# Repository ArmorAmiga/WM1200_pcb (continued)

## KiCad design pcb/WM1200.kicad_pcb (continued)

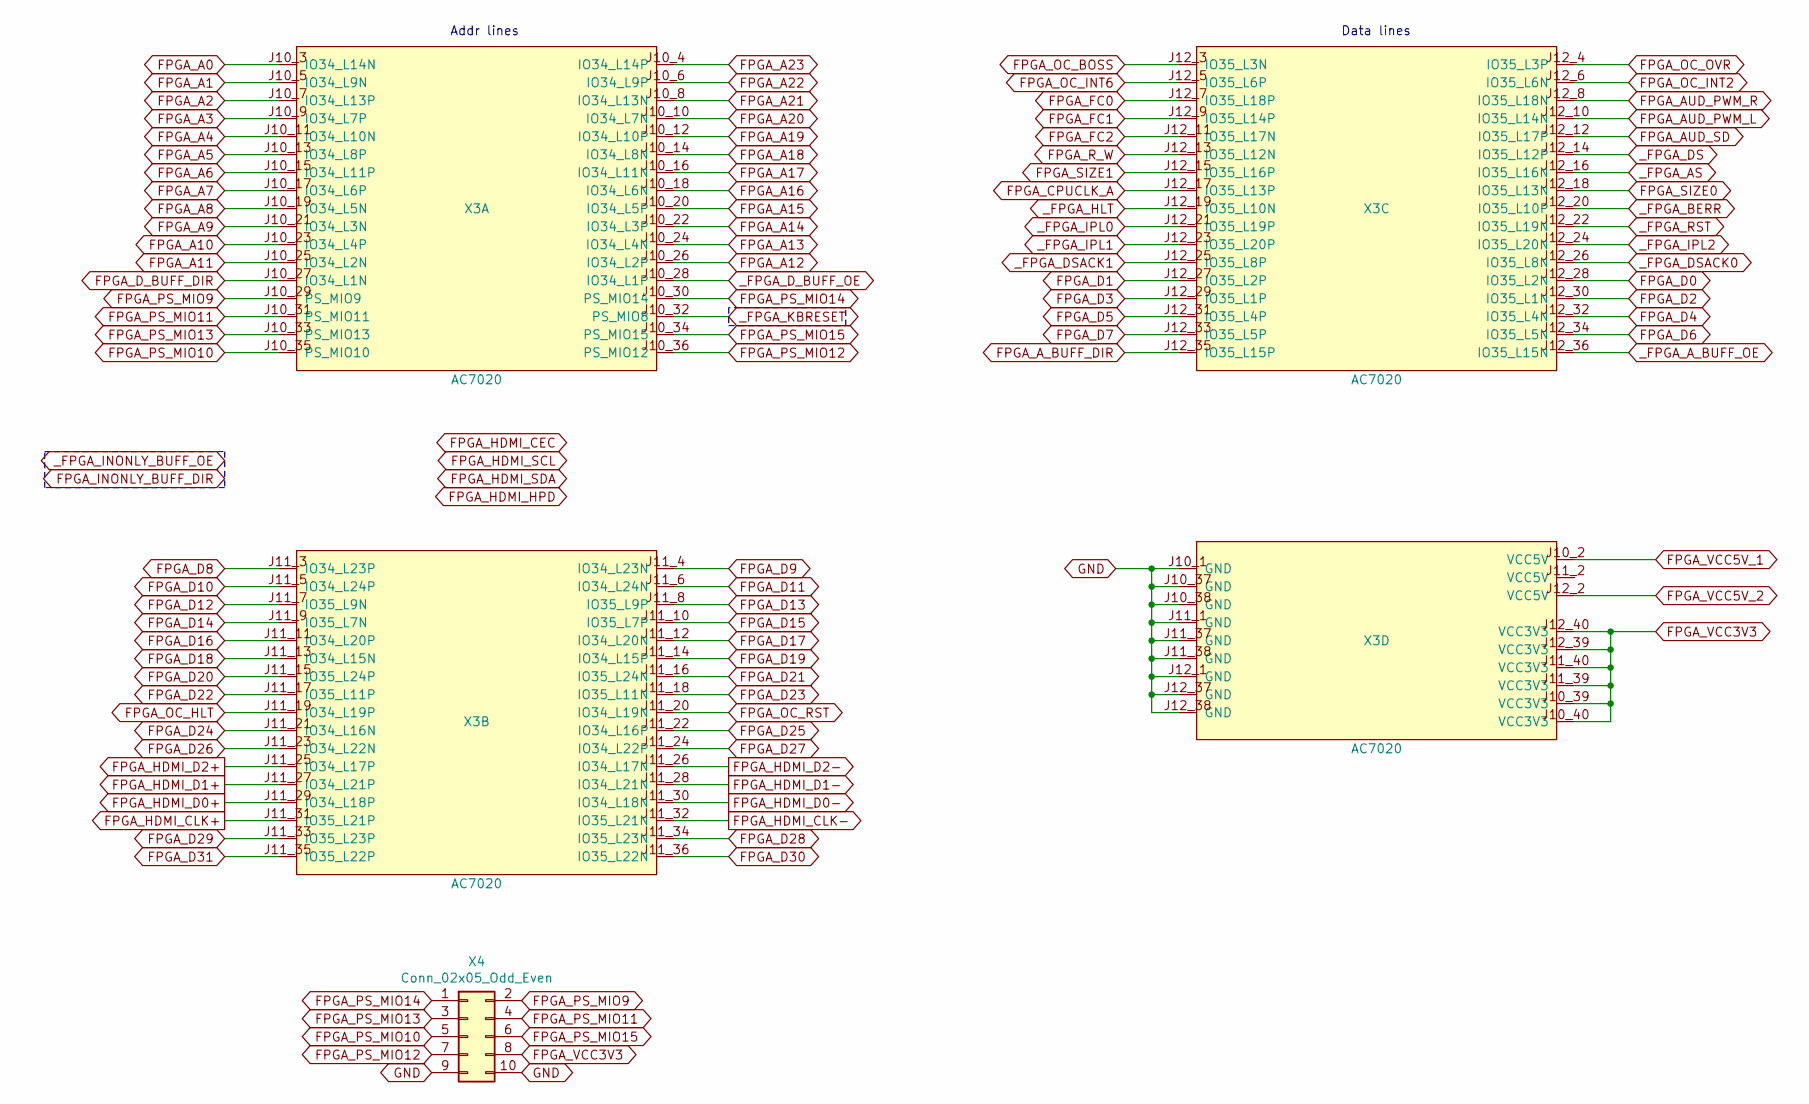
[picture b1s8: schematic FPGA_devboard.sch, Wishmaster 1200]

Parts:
X3: AC7020; ac7020
X4: Conn_02x05_Odd_Even; PinHeader_2x05_P2.54mm_Vertical

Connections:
FPGA_A0: X3.J10_3 (IO34_L14N); also elsewhere on the board
FPGA_A1: X3.J10_5 (IO34_L9N); also elsewhere on the board
FPGA_A2: X3.J10_7 (IO34_L13P); also elsewhere on the board
FPGA_A3: X3.J10_9 (IO34_L7P); also elsewhere on the board
FPGA_A4: X3.J10_11 (IO34_L10N); also elsewhere on the board
FPGA_A5: X3.J10_13 (IO34_L8P); also elsewhere on the board
FPGA_A6: X3.J10_15 (IO34_L11P); also elsewhere on the board
FPGA_A7: X3.J10_17 (IO34_L6P); also elsewhere on the board
FPGA_A8: X3.J10_19 (IO34_L5N); also elsewhere on the board
FPGA_A9: X3.J10_21 (IO34_L3N); also elsewhere on the board
FPGA_A10: X3.J10_23 (IO34_L4P); also elsewhere on the board
FPGA_A11: X3.J10_25 (IO34_L2N); also elsewhere on the board
FPGA_A12: X3.J10_26 (IO34_L2P); also elsewhere on the board
FPGA_A13: X3.J10_24 (IO34_L4N); also elsewhere on the board
FPGA_A14: X3.J10_22 (IO34_L3P); also elsewhere on the board
FPGA_A15: X3.J10_20 (IO34_L5P); also elsewhere on the board
FPGA_A16: X3.J10_18 (IO34_L6N); also elsewhere on the board
FPGA_A17: X3.J10_16 (IO34_L11N); also elsewhere on the board
FPGA_A18: X3.J10_14 (IO34_L8N); also elsewhere on the board
FPGA_A19: X3.J10_12 (IO34_L10P); also elsewhere on the board
FPGA_A20: X3.J10_10 (IO34_L7N); also elsewhere on the board
FPGA_A21: X3.J10_8 (IO34_L13N); also elsewhere on the board
FPGA_A22: X3.J10_6 (IO34_L9P); also elsewhere on the board
FPGA_A23: X3.J10_4 (IO34_L14P); also elsewhere on the board
FPGA_AUD_PWM_L: X3.J12_10 (IO35_L14N); also elsewhere on the board
FPGA_AUD_PWM_R: X3.J12_8 (IO35_L18N); also elsewhere on the board
FPGA_AUD_SD: X3.J12_12 (IO35_L17P); also elsewhere on the board
FPGA_A_BUFF_DIR: X3.J12_35 (IO35_L15P); also elsewhere on the board
FPGA_CPUCLK_A: X3.J12_17 (IO35_L13P); also elsewhere on the board
FPGA_D0: X3.J12_28 (IO35_L2N); also elsewhere on the board
FPGA_D1: X3.J12_27 (IO35_L2P); also elsewhere on the board
FPGA_D2: X3.J12_30 (IO35_L1N); also elsewhere on the board
FPGA_D3: X3.J12_29 (IO35_L1P); also elsewhere on the board
FPGA_D4: X3.J12_32 (IO35_L4N); also elsewhere on the board
FPGA_D5: X3.J12_31 (IO35_L4P); also elsewhere on the board
FPGA_D6: X3.J12_34 (IO35_L5N); also elsewhere on the board
FPGA_D7: X3.J12_33 (IO35_L5P); also elsewhere on the board
FPGA_D8: X3.J11_3 (IO34_L23P); also elsewhere on the board
FPGA_D9: X3.J11_4 (IO34_L23N); also elsewhere on the board
FPGA_D10: X3.J11_5 (IO34_L24P); also elsewhere on the board
FPGA_D11: X3.J11_6 (IO34_L24N); also elsewhere on the board
FPGA_D12: X3.J11_7 (IO35_L9N); also elsewhere on the board
FPGA_D13: X3.J11_8 (IO35_L9P); also elsewhere on the board
FPGA_D14: X3.J11_9 (IO35_L7N); also elsewhere on the board
FPGA_D15: X3.J11_10 (IO35_L7P); also elsewhere on the board
FPGA_D16: X3.J11_11 (IO34_L20P); also elsewhere on the board
FPGA_D17: X3.J11_12 (IO34_L20N); also elsewhere on the board
FPGA_D18: X3.J11_13 (IO34_L15N); also elsewhere on the board
FPGA_D19: X3.J11_14 (IO34_L15P); also elsewhere on the board
FPGA_D20: X3.J11_15 (IO35_L24P); also elsewhere on the board
FPGA_D21: X3.J11_16 (IO35_L24N); also elsewhere on the board
FPGA_D22: X3.J11_17 (IO35_L11P); also elsewhere on the board
FPGA_D23: X3.J11_18 (IO35_L11N); also elsewhere on the board
FPGA_D24: X3.J11_21 (IO34_L16N); also elsewhere on the board
FPGA_D25: X3.J11_22 (IO34_L16P); also elsewhere on the board
FPGA_D26: X3.J11_23 (IO34_L22N); also elsewhere on the board
FPGA_D27: X3.J11_24 (IO34_L22P); also elsewhere on the board
FPGA_D28: X3.J11_34 (IO35_L23N); also elsewhere on the board
FPGA_D29: X3.J11_33 (IO35_L23P); also elsewhere on the board
FPGA_D30: X3.J11_36 (IO35_L22N); also elsewhere on the board
FPGA_D31: X3.J11_35 (IO35_L22P); also elsewhere on the board
FPGA_D_BUFF_DIR: X3.J10_27 (IO34_L1N); also elsewhere on the board
FPGA_FC0: X3.J12_7 (IO35_L18P); also elsewhere on the board
FPGA_FC1: X3.J12_9 (IO35_L14P); also elsewhere on the board
FPGA_FC2: X3.J12_11 (IO35_L17N); also elsewhere on the board
FPGA_HDMI_CLK+: X3.J11_31 (IO35_L21P); also elsewhere on the board
FPGA_HDMI_CLK-: X3.J11_32 (IO35_L21N); also elsewhere on the board
FPGA_HDMI_D0+: X3.J11_29 (IO34_L18P); also elsewhere on the board
FPGA_HDMI_D0-: X3.J11_30 (IO34_L18N); also elsewhere on the board
FPGA_HDMI_D1+: X3.J11_27 (IO34_L21P); also elsewhere on the board
FPGA_HDMI_D1-: X3.J11_28 (IO34_L21N); also elsewhere on the board
FPGA_HDMI_D2+: X3.J11_25 (IO34_L17P); also elsewhere on the board
FPGA_HDMI_D2-: X3.J11_26 (IO34_L17N); also elsewhere on the board
FPGA_OC_BOSS: X3.J12_3 (IO35_L3N); also elsewhere on the board
FPGA_OC_HLT: X3.J11_19 (IO34_L19P); also elsewhere on the board
FPGA_OC_INT2: X3.J12_6 (IO35_L6N); also elsewhere on the board
FPGA_OC_INT6: X3.J12_5 (IO35_L6P); also elsewhere on the board
FPGA_OC_OVR: X3.J12_4 (IO35_L3P); also elsewhere on the board
FPGA_OC_RST: X3.J11_20 (IO34_L19N); also elsewhere on the board
FPGA_PS_MIO9: X3.J10_29 (PS_MIO9), X4.2
FPGA_PS_MIO10: X3.J10_35 (PS_MIO10), X4.5
FPGA_PS_MIO11: X3.J10_31 (PS_MIO11), X4.4
FPGA_PS_MIO12: X3.J10_36 (PS_MIO12), X4.7
FPGA_PS_MIO13: X3.J10_33 (PS_MIO13), X4.3
FPGA_PS_MIO14: X3.J10_30 (PS_MIO14), X4.1
FPGA_PS_MIO15: X3.J10_34 (PS_MIO15), X4.6
FPGA_R_W: X3.J12_13 (IO35_L12N); also elsewhere on the board
FPGA_SIZE0: X3.J12_18 (IO35_L13N); also elsewhere on the board
FPGA_SIZE1: X3.J12_15 (IO35_L16P); also elsewhere on the board
FPGA_VCC3V3: X3.J10_39 (VCC3V3), X3.J10_40 (VCC3V3), X3.J11_39 (VCC3V3), X3.J11_40 (VCC3V3), X3.J12_39 (VCC3V3), X3.J12_40 (VCC3V3), X4.8; also elsewhere on the board
FPGA_VCC5V_1: X3.J10_2 (VCC5V); also elsewhere on the board
FPGA_VCC5V_2: X3.J12_2 (VCC5V); also elsewhere on the board
GND: X3.J10_1 (GND), X3.J10_37 (GND), X3.J10_38 (GND), X3.J11_1 (GND), X3.J11_37 (GND), X3.J11_38 (GND), X3.J12_1 (GND), X3.J12_37 (GND), X3.J12_38 (GND), X4.9, X4.10; also elsewhere on the board
_FPGA_AS: X3.J12_16 (IO35_L16N); also elsewhere on the board
_FPGA_A_BUFF_OE: X3.J12_36 (IO35_L15N); also elsewhere on the board
_FPGA_BERR: X3.J12_20 (IO35_L10P); also elsewhere on the board
_FPGA_DS: X3.J12_14 (IO35_L12P); also elsewhere on the board
_FPGA_DSACK0: X3.J12_26 (IO35_L8N); also elsewhere on the board
_FPGA_DSACK1: X3.J12_25 (IO35_L8P); also elsewhere on the board
_FPGA_D_BUFF_OE: X3.J10_28 (IO34_L1P); also elsewhere on the board
_FPGA_HLT: X3.J12_19 (IO35_L10N); also elsewhere on the board
_FPGA_IPL0: X3.J12_21 (IO35_L19P); also elsewhere on the board
_FPGA_IPL1: X3.J12_23 (IO35_L20P); also elsewhere on the board
_FPGA_IPL2: X3.J12_24 (IO35_L20N); also elsewhere on the board
_FPGA_KBRESET: X3.J10_32 (PS_MIO8); also elsewhere on the board
_FPGA_RST: X3.J12_22 (IO35_L19N); also elsewhere on the board

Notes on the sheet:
Data lines
Addr lines

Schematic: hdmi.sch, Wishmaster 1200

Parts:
C29, C30, C31: 0.1uF 35V; C_0603_1608Metric_Pad1.05x0.95mm_HandSolder
C32: 1nF 250V; C_0603_1608Metric_Pad1.05x0.95mm_HandSolder
R21, R22, R23, R25: 4.7k; R_0603_1608Metric_Pad1.05x0.95mm_HandSolder
R24: 1M; R_0603_1608Metric_Pad1.05x0.95mm_HandSolder
U7: TPD12S016PWR; TSSOP-24_4.4x7.8mm_P0.65mm
X5: HDMI_A; HDMI-19-02F

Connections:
FPGA_HDMI_CEC: U7.1 (CEC_A)
FPGA_HDMI_CLK+: U7.16 (CLK+), X5.10 (CK+); also elsewhere on the board
FPGA_HDMI_CLK-: U7.15 (CLK-), X5.12 (CK-); also elsewhere on the board
FPGA_HDMI_CT_HPD: R23.1, U7.12 (CT_HPD)
FPGA_HDMI_D0+: U7.18 (D0+), X5.7 (D0+); also elsewhere on the board
FPGA_HDMI_D0-: U7.17 (D0-), X5.9 (D0-); also elsewhere on the board
FPGA_HDMI_D1+: U7.21 (D1+), X5.4 (D1+); also elsewhere on the board
FPGA_HDMI_D1-: U7.20 (D1-), X5.6 (D1-); also elsewhere on the board
FPGA_HDMI_D2+: U7.23 (D2+), X5.1 (D2+); also elsewhere on the board
FPGA_HDMI_D2-: U7.22 (D2-), X5.3 (D2-); also elsewhere on the board
FPGA_HDMI_HPD: U7.4 (HPD_A)
FPGA_HDMI_LS_OE: R25.2, U7.5 (LS_OE)
FPGA_HDMI_SCL: R21.1, U7.2 (SCL_A)
FPGA_HDMI_SDA: R22.2, U7.3 (SDA_A)
FPGA_VCC3V3: C31.1, R21.2, R22.1, R23.2, R25.1, U7.24 (VCCA); also elsewhere on the board
FPGA_VCC5V_1: C30.1, U7.11 (VCC5V); also elsewhere on the board
GND: C29.2, C30.2, C31.2, C32.2, R24.2, U7.6 (GND), U7.14 (GND), U7.19 (GND), X5.2 (D2S), X5.5 (D1S), X5.8 (D0S), X5.11 (CKS), X5.17 (GND); also elsewhere on the board
unnamed: C29.1, U7.13 (5V_OUT), X5.18 (+5V)
unnamed: C32.1, R24.1, X5.SH
unnamed: U7.7 (CEC_B), X5.13 (CEC)
unnamed: U7.8 (SCL_B), X5.15 (SCL)
unnamed: U7.9 (SDA_B), X5.16 (SDA)
unnamed: U7.10 (HPD_B), X5.19 (HPD)

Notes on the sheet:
i2c pullup (not sure if i2c will be used here) tpd12s016 seems to have it's own pullups -- not needed?
enable pullups for tpd12s016

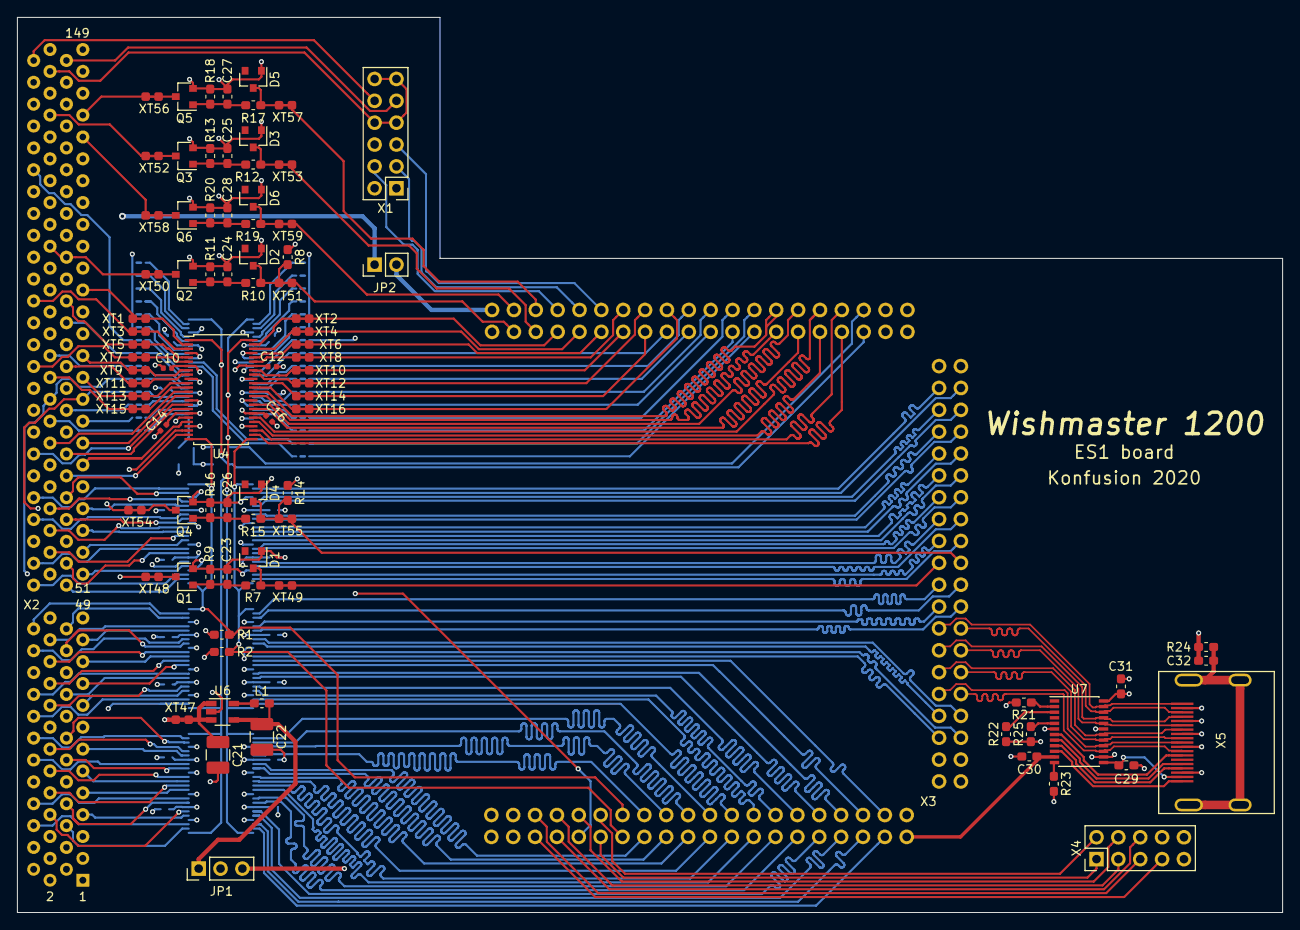
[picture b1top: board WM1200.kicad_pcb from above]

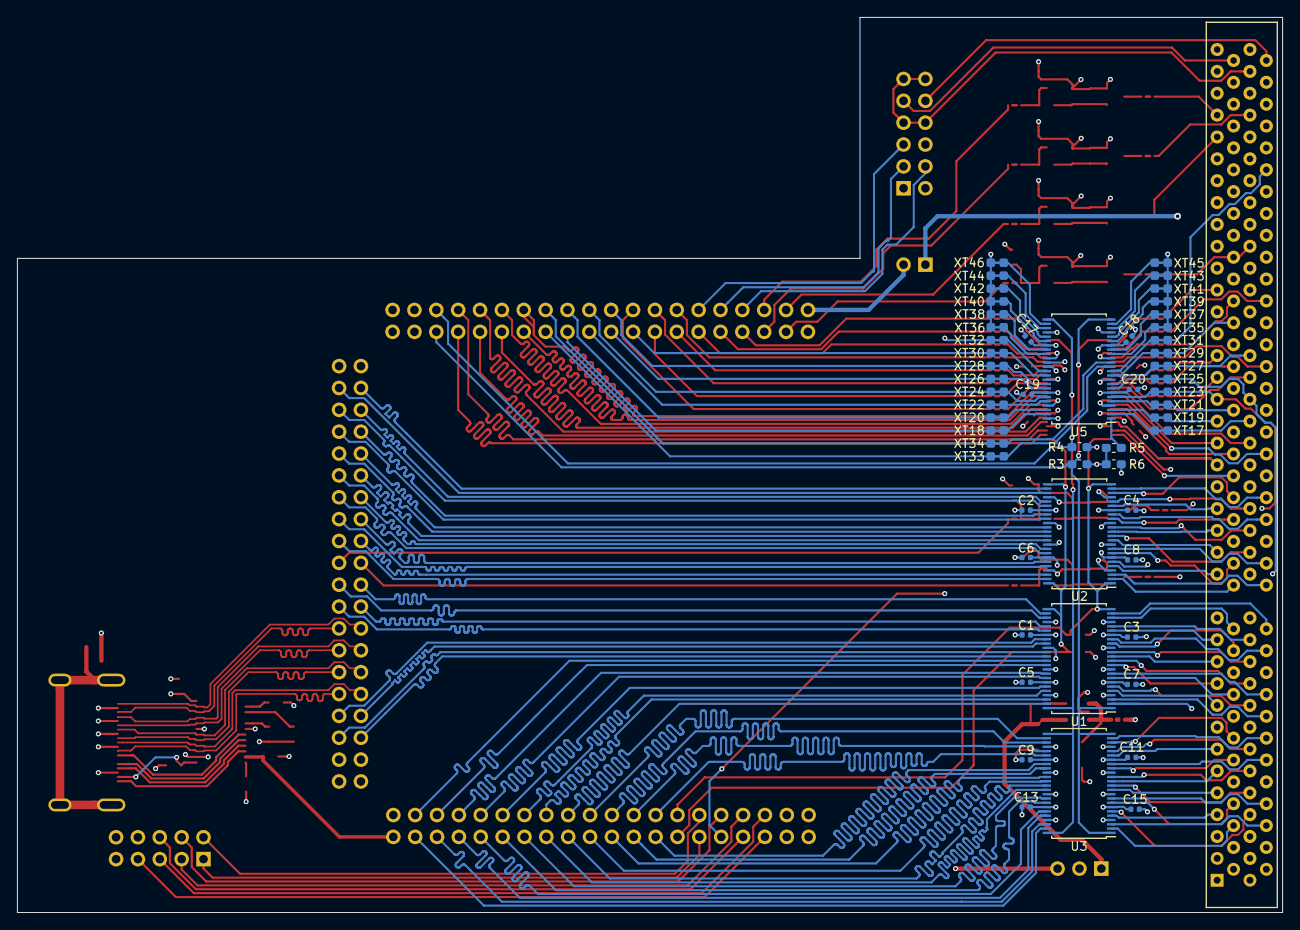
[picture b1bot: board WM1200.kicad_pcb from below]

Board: 4 copper layers, 147.0 x 104.0 mm, 143 parts (54 on the bottom side), 268 nets.

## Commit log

2020-02-24 ok, here we go
2020-02-25 hierarchy updated
2020-02-25 74LVCH162245A symbol added
2020-02-25 new sch lists
2020-02-25 Revert "new sch lists"
    This reverts commit 63e92f37236e6046a75a91c77abd2eec0f4ea4c7.
2020-02-25 some work on sheets
2020-02-25 new list added for power converters
2020-02-25 hiererchy update
2020-02-25 buffer section finished, audio moved to expansion connector
2020-02-25 some work done on "open collector" list
2020-02-25 cosmetical changes in buffers sch's
2020-02-25 AC7020 schlib and sch list updated
2020-02-26 scheme update
2020-02-26 FPGA side labels added
2020-02-26 bus name typo fixed on audio sheet
2020-02-26 Some work done on the whole project
2020-02-26 The scheme needs it's buses to be remade because of the way KiCad works, ok
2020-02-26 wip commit (sync work between pc's)
2020-02-28 ok, we are using global labels now
2020-02-28 fpga-side gpio connector added
2020-02-28 Some more changes wip
2020-02-29 hdmi list added
2020-02-29 yet another wip commit
2020-03-01 open collector list finished
2020-03-01 pinout changes
2020-03-01 started to design pcb and footprints
2020-03-01 changed pullup resistance and zener diodes voltage at OC list
2020-03-02 testpoints footprints added, some footprints assigned
2020-03-02 more footprints assigned
2020-03-02 more footprints assigned, caps added into open collector base circuit
2020-03-02 hdmi footprint added, ac7020 footprint added, but not finished yet
2020-03-02 ac7020 footprint finished
2020-03-02 working on pcb
2020-03-03 working on pcb 2
2020-03-03 clockport fancy 3d model added
2020-03-05 Board pcb updated
2020-03-05 clockport removed from ES1 pcb design (maybe another time)
2020-03-05 SCH comments updated
2020-03-05 Ground plane added
2020-03-05 Sync work
2020-03-05 some work on hdmi part
2020-03-05 some more work done
2020-03-06 Buffers power scheme rework in progress, re-annotate board
2020-03-06 Unused buffer io are now grounded via testpads
2020-03-06 Some work done, sync
2020-03-06 still working
2020-03-08 some dirty routing
2020-03-08 time to stop for today
2020-03-09 wire length aligns
2020-03-11 Some more work done
    I'm too lazy to think about commit messages in my pet project, really
2020-03-11 bigger vias, fixing DRC issues
2020-03-12 DRC passed
2020-03-12 rerouted one trace, sync
2020-03-16 ready for production
2020-03-16 board updated - factory DRC checking in progress
2020-03-16 factory DRC passed
2020-03-16 gerber files uploaded
2020-03-17 remind myself to connect CPUCLK to clock-capable pin in the future board revisions
2020-10-28 I'm too lazy to create a normal BOM. so here's an auto-generated one
